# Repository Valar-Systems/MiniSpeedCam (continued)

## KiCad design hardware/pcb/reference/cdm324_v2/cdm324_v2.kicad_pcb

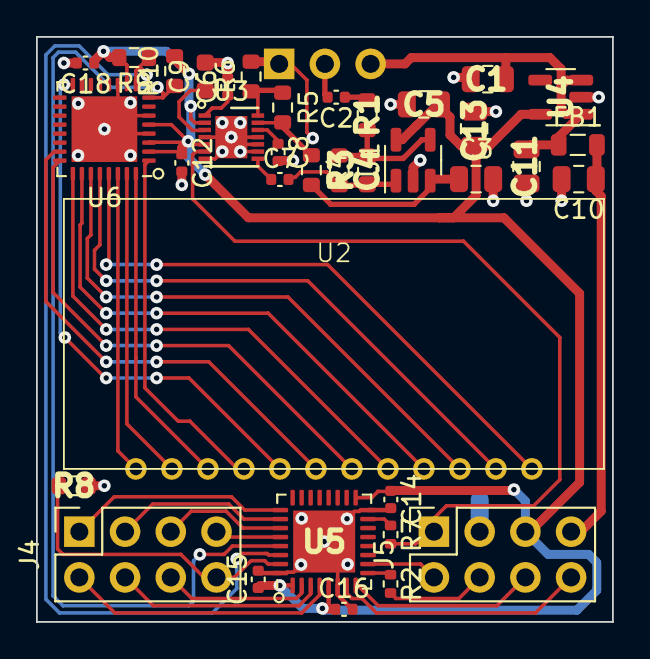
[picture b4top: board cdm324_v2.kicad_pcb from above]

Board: 2 copper layers, 32.0 x 32.5 mm, 37 parts (1 on the bottom side), 44 nets.

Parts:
C1, C3, C5, C10, C11, C13: 22uF; C_0805_2012Metric
C2, C6, C7, C8, C12, C14, C15, C16, C18: 470nF; C_0402_1005Metric
C4: 200p; C_0603_1608Metric
C9: 2.2uF; C_0603_1608Metric
FB1: Ferrite_Bead; L_0805_2012Metric
J2: Conn_01x03_Female; PinHeader_1x03_P2.54mm_Vertical
J4, J5: Conn_02x04_Odd_Even; PinSocket_2x04_P2.54mm_Vertical
R1, R4, R8, R9, R10: 4k7; R_0603_1608Metric
R2, R7: 75; R_0402_1005Metric
R3, R5, R6: 130k; R_0603_1608Metric
U1: LMP7731; SOT-23-5
U2: TN_DISPLAY
U3: MAX9814; DFN-14-1EP_3x3mm_P0.4mm_EP1.78x2.35mm
U4: NCP163ASN330T1G; SOT-23-5
U5: STM32F301K8Ux; QFN-32-1EP_5x5mm_P0.5mm_EP3.45x3.45mm
U6: QFN-32-1EP_5x5mm_P0.5mm_EP3.65x3.65mm

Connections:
+3V3: C5.1, C12.1, C13.1, C14.1, C15.1, C16.1, C18.1, J5.5, R9.2, R10.2, U1.5 (V+), U3.2 (~SHDN), U3.5 (VDD), U4.5 (OUT), U5.1 (VDD), U5.5 (VDDA), U5.17 (VDD), U6.2 (VLCD), U6.3 (VDD), U6.5 (nRST), U6.10 (PORE)
+5V: C1.1, C11.1, FB1.1, J2.3, U4.1 (IN), U4.3 (EN)
/BOOT0: J4.8, R8.2, U5.31 (BOOT0)
/DISP_5: U2.5, U6.16 (SEG4)
/DISP_6: U2.6, U6.23 (SEG11)
/DISP_7: U2.7, U6.24 (SEG12)
/DISP_8: U2.8, U6.25 (SEG13)
/DISP_9: U2.9, U6.26 (SEG14)
/DISP_10: U2.10, U6.27 (SEG15)
/DISP_11: U2.11, U6.28 (SEG16)
/DISP_12: U2.12, U6.29 (SEG17)
/DISP_COM1: U2.1 (COM1), U6.30 (COM0)
/DISP_COM2: U2.2 (COM2), U6.31 (COM1)
/DISP_COM3: U2.3 (COM3), U6.32 (COM2)
/DISP_COM4: U2.4 (COM4), U6.1 (COM3)
/I2C1_SCL: R10.1, U5.29 (PB6), U6.8 (SCL)
/I2C1_SDA: R9.1, U5.30 (PB7), U6.9 (SDA)
/PA0: J5.8, U5.7 (PA0)
/PA1: J5.6, U5.8 (PA1)
/PA15: J4.1, U5.25 (PA15)
/PB3: J4.3, U5.26 (PB3)
/PB4: J4.5, U5.27 (PB4)
/PB5: J4.7, U5.28 (PB5)
/PF0: J4.6, U5.2 (PF0)
/PF1: J4.4, U5.3 (PF1)
/USART2_BL_RX: J5.2, U5.10 (PA3)
/USART2_BL_TX: R2.1, U5.9 (PA2)
/VOUT: J5.1, R7.2, U3.6 (MICOUT)
/nRESET: J4.2, U5.4 (NRST)
GND: C1.2, C3.2, C5.2, C6.2, C8.2, C9.2, C10.2, C11.2, C12.2, C13.2, C14.2, C15.2, C16.2, C18.2, J2.1, J5.3, R6.2, R8.1, U1.2 (V-), U3.4 (GND), U3.7 (GND), U3.9 (A/R), U3.10 (GAIN), U3.11 (GND), U3.15 (GND), U4.2 (GND), U5.6 (VSSA), U5.16 (VSS), U5.32 (VSS), U5.33 (VSS), U6.4 (VSS), U6.6 (A0), U6.11 (A1), U6.33 (VSS)
unnamed: C2.1, R1.2
unnamed: C4.1, C7.2, R3.1, U1.1
unnamed: C2.2, J2.2
unnamed: J5.4, R2.2
unnamed: C3.1, R4.2, U1.3 (+)
unnamed: C4.2, R1.1, R3.2, U1.4 (-)
unnamed: C8.1, U3.12 (BIAS)
unnamed: C9.1, U3.3 (CG)
unnamed: C6.1, U3.1 (CT)
unnamed: R4.1, R5.2, U3.13 (MICBIAS)
unnamed: C7.1, U3.8 (MICIN)
unnamed: R5.1, R6.1, U3.14 (TH)
unnamed: R7.1, U5.15 (PB0)
VCC: C10.1, FB1.2, J5.7

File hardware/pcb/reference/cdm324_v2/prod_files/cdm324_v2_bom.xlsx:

Item # | Qty | Designator | Value | Manufacturer | Manufacturer Part Number | Alternative LCSC part number | Package/Footprint | Digikey Link
1 | 6 | C1, C3, C5, C10, C11, C13 | 22uF | Samsung Electro-Mechanics | CL21A226MOCLRNC | C602037 | 0805 | https://www.digikey.com/product-detail/en/samsung-electro-me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
2 | 1 | C4 | 27pF | YAGEO | CC0603JRNPO9BN270 | C107045 | 0603 | https://www.digikey.com/en/products/detail/yageo/CC0603JRNPO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
3 | 9 | C2, C6, C7, C8, C12, C14, C15, C16, C18 | 470nF | TDK Corporation | C1005X5R1E474K050BB | C92361 | 0402 | https://www.digikey.com/en/products/detail/tdk-corporation/C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
4 | 1 | C9 | 2.2uF | Murata Electronics | GRM188R71A225KE15D | C1607 | 0603 | https://www.digikey.com/en/products/detail/murata-electronic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
5 | 1 | FB1 | Ferrite_Bead | Laird-Signal Integrity Products | HZ0805D102R-10 | C44838 | 0805 | http://www.digikey.com/product-detail/en/HZ0805D102R-10/240-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
6 | 1 | J2 | Conn_01x03_Female | Sullins Connector Solutions | PPPC031LFBN-RC | C146243 |  | http://www.digikey.com/product-detail/en/sullins-connector-s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
7 | 2 | J4, J5 | Conn_02x04_Odd_Even | Sullins Connector Solutions | PPPC042LFBN-RC | C92271 |  | https://www.digikey.com/en/products/detail/sullins-connector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
8 | 5 | R1, R4, R8, R9, R10 | 4k7 | YAGEO | RC0603FR-074K7L | C99782 | 0603 | https://www.digikey.com/en/products/detail/yageo/RC0603FR-07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
9 | 2 | R2, R7 | 75 | YAGEO | RC0402JR-0775RL | C137841 | 0402 | https://www.digikey.com/en/products/detail/yageo/RC0402JR-07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
10 | 2 | R5, R6 | 130k | Panasonic Electronic Components | ERJ-3EKF1303V | C163432 | 0603 | https://www.digikey.com/product-detail/en/panasonic-electron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
11 | 1 | U1 | LMP7731 | Texas Instruments | LMP7731MF/NOPB | C202252 |  | https://www.digikey.ch/en/products/detail/texas-instruments/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
12 | 1 | U3 | MAX9814 | Analog Devices Inc./Maxim Integrated | MAX9814ETD+T | C41714 |  | https://www.digikey.com/en/products/detail/analog-devices-in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
13 | 1 | U4 | NCP163ASN330T1G | onsemi | NCP163ASN330T1G | C603656 |  | https://www.digikey.com/product-detail/en/on-semiconductor/N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
14 | 1 | U5 | STM32F301K8Ux | STMicroelectronics | STM32F301K8U6 | C111684 |  | https://www.digikey.com/product-detail/en/stmicroelectronics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
15 | 1 | U6 | PCA8561AHN/AY | NXP USA Inc. | PCA8561AHN/AY | C2653710 |  | https://www.digikey.ch/en/products/detail/nxp-usa-inc/PCA856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
16 | 1 | U2 | 12PIN TN Positive 4-Digits |  |  |  |  | https://www.aliexpress.com/item/1005003060952508.html
17 | 1 | R3 | 620k | YAGEO | RC0603FR-07620KL | C68737 | 0603

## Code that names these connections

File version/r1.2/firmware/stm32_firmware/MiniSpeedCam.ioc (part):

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Mcu.Name=STM32F301K(6-8)Ux
Mcu.Package=UFQFPN32
Mcu.UserName=STM32F301K8Ux
PA10.Mode=Asynchronous
PA10.Signal=USART1_RX
PA2.Mode=Asynchronous
PA2.Signal=USART2_TX
PA3.Mode=Asynchronous
PA3.Signal=USART2_RX
PA5.Signal=GPIO_Output
PA9.Mode=Asynchronous
PA9.Signal=USART1_TX
PB0.GPIOParameters=GPIO_Label
PB0.GPIO_Label=DOPPLER
PB0.Mode=IN11-Single-Ended
PB0.Signal=ADC1_IN11
RCC.HSEPLLFreq_Value=8000000
RCC.HSE_VALUE=8000000
RCC.SYSCLKFreq_VALUE=64000000
RCC.SYSCLKSourceVirtual=RCC_SYSCLKSOURCE_PLLCLK
board=custom

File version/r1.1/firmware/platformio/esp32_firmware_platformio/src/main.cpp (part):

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#include "esp_system.h"        // esp_reset_reason()

// --- GPIO assignments (board revision 1.1) ---
#define STM32_RESET_PIN GPIO_NUM_47  // Drives STM32 NRST low to reset the radar MCU
#define STM32_BOOT0_PIN GPIO_NUM_14  // Drives STM32 BOOT0 (HIGH = ROM bootloader) for ESP-driven flashing
#define RX_GPIO 42                   // UART1 RX from STM32 (speed reports)
#define TX_GPIO 41                   // UART1 TX to STM32 (speed query commands)
#define ESP_WAKEUP_PIN GPIO_NUM_1    // STM32 pulls HIGH when motion >= ~5mph is detected
#define STM_WAKEUP_PIN GPIO_NUM_2    // (was the reserved STM_WAKEUP line; now the radar-blank line below)
#define RADAR_BLANK_PIN STM_WAKEUP_PIN  // ESP -> STM32 PA4: HIGH during WiFi bursts so the STM32 discards rail-corrupted FFT frames
#define WIFI_RESET_PIN GPIO_NUM_21   // Active-low button: hold 3s to clear stored WiFi creds

#define CAMERA_PWDN_PIN GPIO_NUM_45  // OV2640 power-down (active high)
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  Serial.printf("[BOOT] heap=%u psram=%u\n", (unsigned)ESP.getFreeHeap(), (unsigned)ESP.getFreePsram());

  // GPIO setup
  pinMode(ESP_WAKEUP_PIN, INPUT);
  pinMode(WIFI_RESET_PIN, INPUT_PULLUP);  // Active-low button; enable internal pull-up so the pin idles HIGH (no spurious resets)
  pinMode(STM32_RESET_PIN, OUTPUT);
  pinMode(STM32_BOOT0_PIN, OUTPUT);
  digitalWrite(STM32_BOOT0_PIN, LOW);  // BOOT0 low = STM32 boots from flash (normal run)
  pinMode(RADAR_BLANK_PIN, OUTPUT);
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  pinMode(CAMERA_RST_PIN, OUTPUT);   // Set the camera reset pin // Causes crash

  // Light Sleep setup
  //esp_sleep_enable_ext0_wakeup(ESP_WAKEUP_PIN, 1);  // Wake up ESP32 when GPIO1 is HIGH //STM will always pull GIO1 high when speeds above 5 mph are detected. Will pull low when speeds

  // Setup Camera. esp_camera_init() can fail transiently on a marginal power
  // rail, so power-cycle and retry a few times rather than booting blind with
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  Serial.setDebugOutput(false);

  // Reset CDM324
  digitalWrite(STM32_RESET_PIN, LOW);
  issue_cdm324_reset();

  // Read the STM32 firmware version now (before taskCore1 starts polling, so it
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        // grace window simply restarts once Core 0 goes quiet / the radar is back.
        if (coreNetBusy() || stmLinkDead()) {
          sleep_time = millis() + 5000;
        } else if (digitalRead(ESP_WAKEUP_PIN) == 0) {  // Only if STM not measuring data
          wake_flag = false;
          Serial.println("[PWR] idle: WiFi off (post-boot grace elapsed)");

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    }

    // Checks if wifi is disconnected and sets connect flag to true. Connection will occur on Core 0
    if (digitalRead(ESP_WAKEUP_PIN) == 1) { // Check if speed detected on radar first. Use interrupt for this instead?
      // Only request a reconnect when we actually have credentials to use.
      // In AP config mode (ssid == "NOT_SET") WiFi.status() is never
      // WL_CONNECTED, so without this guard we'd flag a reconnect every loop
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
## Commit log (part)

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2026-01-04 Reduce sleep delay and add enclosure guide
    Changed device sleep delay from 120 seconds to 10 seconds in the ESP32 firmware for quicker testing or development. Added a new enclosure guide text file in the hardware directory.
2026-01-06 Add CERN Open Hardware Licence Version 2
    Added CERN Open Hardware Licence Version 2 - Strongly Reciprocal to the project.
2026-01-06 Created hardware versions
2026-01-06 Revise README for MiniSpeedCam R1.0
    Updated README.md for MiniSpeedCam R1.0 with new information on flashing and device operation.
2026-01-06 Revise README for MiniSpeedCam R1.1
    Updated README for MiniSpeedCam R1.1 to include hardware issue details and reflashing instructions.
2026-01-06 Update README with USB sleep mode documentation link
    Added a link to documentation regarding USB sleep mode issues.
2026-01-06 Update README with ESP32 upload settings
2026-01-06 Fix formatting in README for ESP32 upload settings
2026-01-06 Update README with ESP32 sleep mode instructions
    Added note about needing to restart Arduino after ESP32 sleep mode.
2026-01-09 Refactor photo function and update sleep logic
    Renamed takeSendPhoto() to sendPhoto() for clarity and updated all references. Commented out light sleep and related code in esp32_firmware.ino for version 1.1, replacing sleep with Wi-Fi disconnect 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
2026-05-08 New 1.2 version hardware
2026-05-08 Update README for MiniSpeedCam to version R1.2
    Updated README to reflect changes in hardware version from R1.1 to R1.2, including removal of outdated information about sleep mode issues.
2026-05-08 fixed pin number
2026-05-08 Fixed position file
2026-05-08 Updated schematic
2026-05-08 Add documentation to ESP32 Arduino firmware
    Add file headers, function-level docstrings, and variable comments
    across the r1.0, r1.1, and r1.2 ESP32 sketches and their helper
    headers (variables.h, camera.h, radar.h, api.h, espui_settings.h).
    Documents the dual-core task split, the UART protocol with the STM32,
    the OV2640 capture path, the WiFi/AP fallback flow, and the ESPUI
    config controls. Code is unchanged.
2026-05-08 Turned sleep back on
2026-05-08 Fix bugs in ESP32 v1.2 firmware
    - api.h: reserve() was called on the wrong String (httpsRequestData
    instead of httpsRequestSend), forcing many reallocations during the
    ~100KB photo upload payload build.
    - api.h: release photo_base64 after upload so the buffer doesn't sit
    on the heap until the next capture.
    - api.h: round maxSpeed -> speed_actual to keep the wire format integer
2026-05-08 Remove unused globals from ESP32 v1.2 firmware
    Dropped twelve unused globals from variables.h (API_photo,
    photo_finished, sleep_idle_time, send_alert, lastTime, labelWifi,
    display_wifi, button1, switchOne, status, apIP, DNS_PORT) and the
    write-only send_API (along with its sole assignment in the main
    sketch). The DNS_PORT/apIP pair was apparently intended for a
    captive-portal dnsServer.start() that is never called; the
2026-05-08 Wire up captive-portal DNS in AP fallback
    dnsServer.processNextRequest() was being called every loop iteration
    but dnsServer.start() had never been invoked, so the captive portal
    silently did nothing - users had to type 192.168.4.1 by hand.
    connectWifiAP() now starts a wildcard DNS responder pointing at the
    soft-AP IP whenever it falls into AP mode, so any DNS lookup from a
    connected client lands on the ESPUI page (and most OSes detect this
2026-05-08 Robustness pass on ESP32 v1.2 firmware
    Five high-impact items from the firmware review:
    - AP-aware idle teardown. The grace-window and 5s-idle paths in
    taskCore1 unconditionally called WiFi.disconnect/WIFI_OFF, which
    killed the soft-AP while a user might still be configuring WiFi
    via the captive portal. Both paths now skip the teardown when
    WiFi.getMode() == WIFI_AP.
2026-05-08 Upload every pass above min_speed, not just photo runs
    send_data was only being raised inside the photo-capture branch, so
    passes that crossed min_speed but never reached photo_speed - and
    passes where takePhoto() failed - never triggered Core 0's upload.
    The non_speeding endpoint was effectively dead.
    Drop the inline send_data assignment and raise send_data once at the
    end of the tracking run. send_photo (already gated on photo_captured)
2026-05-08 Bound CDM324 banner read; add ArduinoOTA support
    issue_cdm324_reset() previously spun forever waiting for a newline
    from the STM32. Because it runs from setup() before either pinned
    task subscribes to the watchdog, a dead or unprogrammed STM32 wedged
    the boot with no recovery. Add a 1000ms millis-based bound and log
    the timeout instead of hanging.
    Also wire up ArduinoOTA so the firmware can be updated without USB.
2026-05-08 Move API bearer token to NVS
    The minispeedcam.com Bubble.io workflow token was hardcoded in api.h
    (twice), so rotating it required reflashing every fielded device.
    Token is now loaded from NVS in setup() with the original baked-in
    value as the default fallback, so existing deployments keep working
    without manual configuration. A new "API Token" text input on the
    WiFi Settings tab lets the operator rotate it from the portal; on
2026-05-08 Add live Status tab to ESPUI portal
    The portal previously had no read-only surface, so debugging a
    device in the field meant USB serial. The new Status tab (added as
    the first tab so it's the landing page) shows live telemetry that
    covers the most common questions:
    - Current Speed - radar reading per polling cycle, in the configured
    unit (mph/kph).
2026-05-08 Enable light sleep mode in firmware
2026-05-08 Use struct-based esp_task_wdt_init on Arduino-ESP32 3.x / IDF 5
    esp_task_wdt_init's signature changed between Arduino-ESP32 2.x
    (IDF 4: timeout_seconds + bool panic) and 3.x (IDF 5: const
    esp_task_wdt_config_t*). The previous commit used the 2.x form,
    which fails to compile on IDF 5.x toolchains:
    error: too many arguments to function
    'esp_err_t esp_task_wdt_init(const esp_task_wdt_config_t*)'
2026-05-21 New Platformio firmware
2026-05-21 Add ArduinoOTA support and unify capture uploads
    Introduce ArduinoOTA-based OTA updates and update partition layout for dual-slot OTA. Adds src/ota.{h,cpp} with otaBegin/otaLoop and a g_ota_in_progress atomic flag; ota callbacks deinit the camera d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
2026-05-21 Add offline queue, diagnostics & upload resiliency
    Introduce offline delivery, runtime diagnostics, and several robustness/usability improvements.
    Key changes:
    - Add LittleFS-backed offline queue (queue.{cpp,h}) and .gitignore for PlatformIO artifacts.
    - Add diagnostics module (diagnostics.{h,cpp}) to record reset reason, boot count, last upload code and formatted uptime.
    - Refactor api: extract apiUploadEventFromMemory(), add optional CA pinning, start NTP sync, rate-limiting, and queue-on-failure logic. Drain queue on WiFi reconnect and periodically from taskCore0.
    - Camera: persist JPEG quality/frame size in NVS, add cameraPowerOff()/On flow and warmup frames, expose getters/setters for
2026-06-02 Add PlatformIO ESP32 firmware (r1.1)
    Introduce a complete PlatformIO project for the MiniSpeedCam ESP32 firmware r1.1. Adds project metadata (.gitignore, .vscode/extensions.json, platformio.ini) and a README with build/board/dependency 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
2026-06-02 Add diagnostics, ESPUI Status tab & power-saver
    Introduce runtime diagnostics and power-management UI: add diagnostics.h (reset reason, boot count, last upload code, uptime formatting) and persist/track boot/upload state. Add Power-Saver Mode (per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
2026-06-02 Enhance WiFi AP/station handling and power
    Enable native USB CDC in platformio.ini and add robustness and safety around WiFi and power behaviors across api.h and main.cpp. Changes include:
    - platformio.ini: enable ARDUINO_USB_MODE and ARDUINO_USB_CDC_ON_BOOT so Serial uses on-chip CDC.
    - api.h: cleanly teardown STA before starting soft-AP (WiFi.disconnect + WIFI_OFF), check softAPConfig(), retry softAP() up to 3 times and log failures to avoid silent AP startup failures.
    - api.h: prevent connectWifi() from switching to STA when no credentials are stored (ssid == "NOT_SET"), preserving the soft-AP for user configuration.
    - api.h: rework wifiResetButton() to be non-blocking using millis() and
2026-06-02 Lower WiFi TX, debounce radar, rate-limit uploads
    Reduce WiFi transmit power to mitigate RF interference with the CDM324 radar front-end (WIFI_TX_POWER set to WIFI_POWER_11dBm and WiFi.setTxPower called in STA/AP paths). Add client-side upload rate 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
2026-06-03 Ported SMT32 to Platformio
2026-06-03 Add diagnostic logging and update platformio configuration
    - Introduced a new log file for diagnostic output from USART2, capturing various metrics including drop rates, magnitudes, and speeds.
    - Updated platformio.ini to configure the serial monitor for USART2, ensuring proper logging and monitoring settings.
    - Added lock files for KiCad PCB and schematic to track user access and modifications.
2026-06-12 moved files
2026-06-20 Update VSCode extensions and add new workspace configuration; remove lock files
2026-06-22 feat(firmware): infer pass direction from echo-energy centroid
    Replace the first-vs-last magnitude compare with a magnitude-weighted echo-index centroid over the whole run, and add a mag_trend (0-100) telemetry field forwarded by sendUpload. Using every echo mak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
